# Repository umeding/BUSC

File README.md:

# BUSC
Boston University Summer Challenge

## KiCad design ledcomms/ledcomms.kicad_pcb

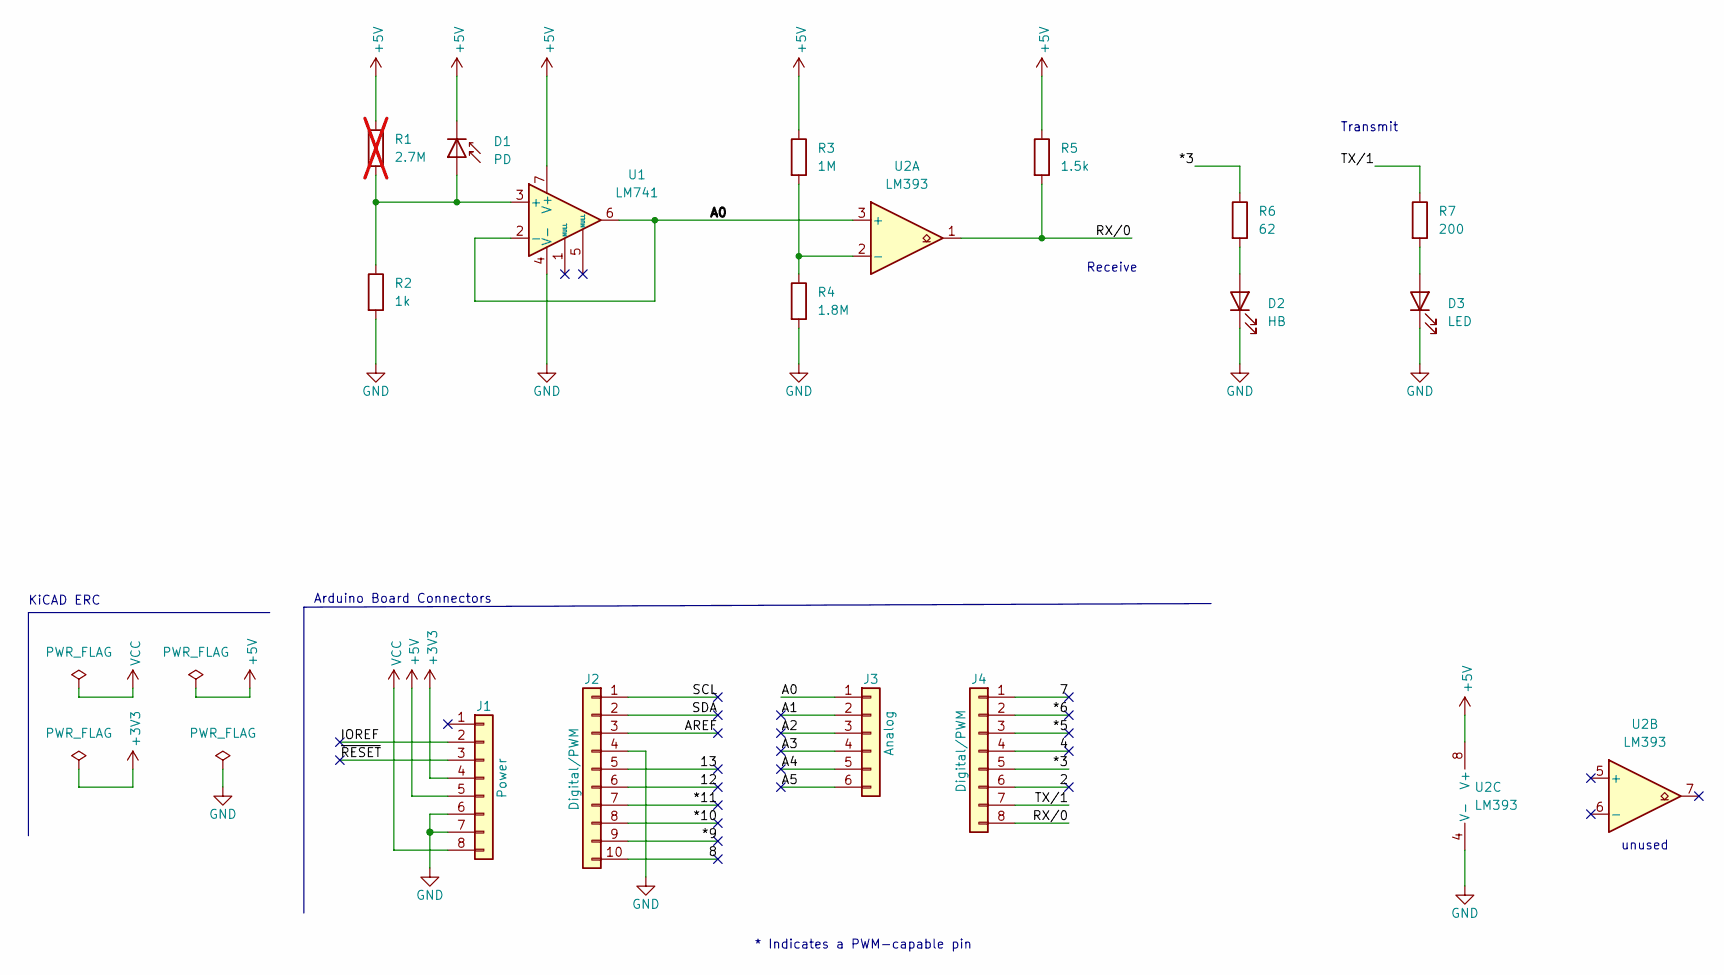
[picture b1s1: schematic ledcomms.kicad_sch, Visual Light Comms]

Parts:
D1: PD; LED_D5.0mm
D2: HB; LED_D5.0mm
D3: LED; LED_D5.0mm
J1: Power; PinSocket_1x08_P2.54mm_Vertical
J2: Digital/PWM; PinSocket_1x10_P2.54mm_Vertical
J3: Analog; PinSocket_1x06_P2.54mm_Vertical
J4: Digital/PWM; PinSocket_1x08_P2.54mm_Vertical
R1: 2.7M; R_Axial_DIN0309_L9.0mm_D3.2mm_P12.70mm_Horizontal; not fitted
R2: 1k; R_Axial_DIN0309_L9.0mm_D3.2mm_P12.70mm_Horizontal
R3: 1M; R_Axial_DIN0309_L9.0mm_D3.2mm_P12.70mm_Horizontal
R4: 1.8M; R_Axial_DIN0309_L9.0mm_D3.2mm_P12.70mm_Horizontal
R5: 1.5k; R_Axial_DIN0309_L9.0mm_D3.2mm_P12.70mm_Horizontal
R6: 62; R_Axial_DIN0309_L9.0mm_D3.2mm_P12.70mm_Horizontal
R7: 200; R_Axial_DIN0309_L9.0mm_D3.2mm_P12.70mm_Horizontal
U1: LM741; DIP-8_W7.62mm_Socket
U2: LM393; DIP-8_W7.62mm_Socket

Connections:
+3V3: J1.4
+5V: D1.1 (K), J1.5, R1.1, R3.1, R5.1, U1.7 (V+), U2.8 (V+)
/2: J4.6
/4: J4.4
/7: J4.1
/8: J2.10
/12: J2.6
/13: J2.5
/*3: J4.5, R6.1
/*5: J4.3
/*6: J4.2
/*9: J2.9
/*10: J2.8
/*11: J2.7
/A0: J3.1, U1.2 (-), U1.6, U2.3 (+)
/A1: J3.2
/A2: J3.3
/A3: J3.4
/A4: J3.5
/A5: J3.6
/AREF: J2.3
/IOREF: J1.2
/RX/0: J4.8, R5.2, U2.1
/SCL: J2.1
/SDA: J2.2
/TX/1: J4.7, R7.1
/~RESET: J1.3
GND: D2.1 (K), D3.1 (K), J1.6, J1.7, J2.4, R2.2, R4.2, U1.4 (V-), U2.4 (V-)
unnamed: D1.2 (A), R1.2, R2.1, U1.3 (+)
unnamed: D2.2 (A), R6.2
unnamed: D3.2 (A), R7.2
unnamed: R3.2, R4.1, U2.2 (-)
VCC: J1.8

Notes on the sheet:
unused
* Indicates a PWM-capable pin
Transmit
KiCAD ERC
Arduino Board Connectors
Receive

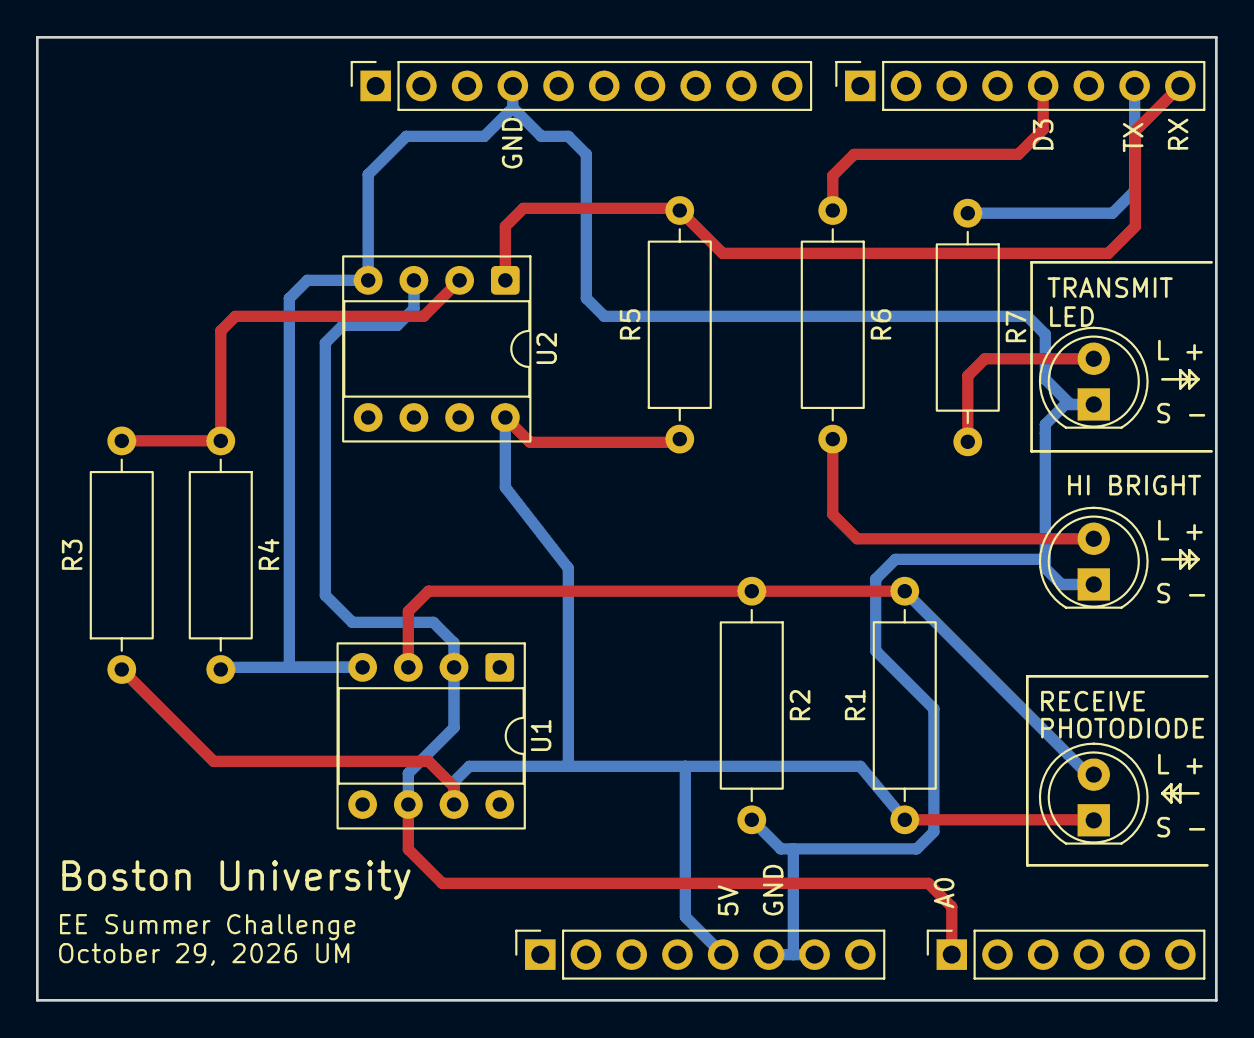
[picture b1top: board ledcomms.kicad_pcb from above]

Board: 2 copper layers, 65.5 x 53.5 mm, 16 parts (0 on the bottom side), 10 nets.

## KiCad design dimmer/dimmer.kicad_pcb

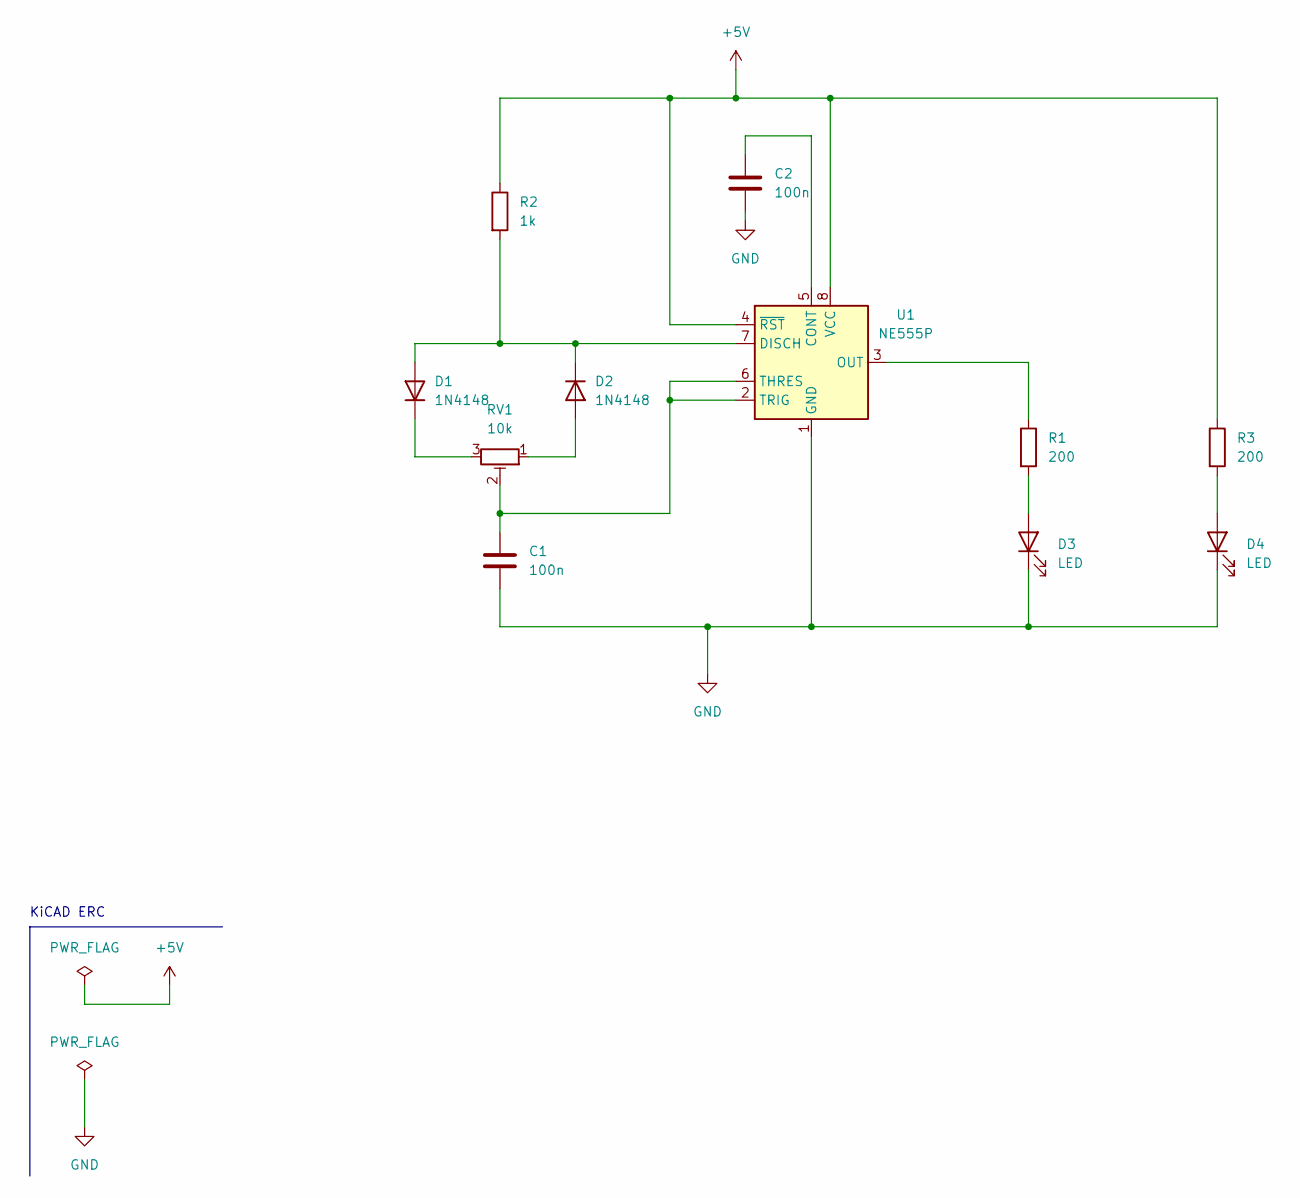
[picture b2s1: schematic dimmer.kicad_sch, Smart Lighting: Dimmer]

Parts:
C1, C2: 100n; C_Disc_D4.7mm_W2.5mm_P5.00mm
D1, D2: 1N4148; D_DO-35_SOD27_P7.62mm_Horizontal
D3, D4: LED; LED_D5.0mm_Clear
R1, R3: 200; R_Axial_DIN0207_L6.3mm_D2.5mm_P10.16mm_Horizontal
R2: 1k; R_Axial_DIN0207_L6.3mm_D2.5mm_P10.16mm_Horizontal
RV1: 10k; Potentiometer_ACP_CA9-V10_Vertical
U1: NE555P; DIP-8_W7.62mm

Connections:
+5V: R2.1, R3.1, U1.4 (~RST), U1.8 (VCC)
GND: C1.2, C2.2, D3.1 (K), D4.1 (K), U1.1 (GND)
unnamed: D1.2 (A), D2.1 (K), R2.2, U1.7 (DISCH)
unnamed: D1.1 (K), RV1.3
unnamed: D2.2 (A), RV1.1
unnamed: D3.2 (A), R1.2
unnamed: D4.2 (A), R3.2
unnamed: C2.1, U1.5 (CONT)
unnamed: R1.1, U1.3 (OUT)
unnamed: C1.1, RV1.2, U1.2 (TRIG), U1.6 (THRES)

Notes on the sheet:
KiCAD ERC

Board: 2 copper layers, 11 parts (0 on the bottom side), 10 nets, no tracks yet.

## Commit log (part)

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2026-05-26 initial
2026-05-26 doc files
2026-06-12 added dimmer circuit
